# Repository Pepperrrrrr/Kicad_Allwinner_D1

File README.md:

# Kicad_Allwinner_D1

kicad测试全志D1高速PCB测试
kicad版本为kicad 6.0
未进行板上其他硬件测试，DDR满速测试完成

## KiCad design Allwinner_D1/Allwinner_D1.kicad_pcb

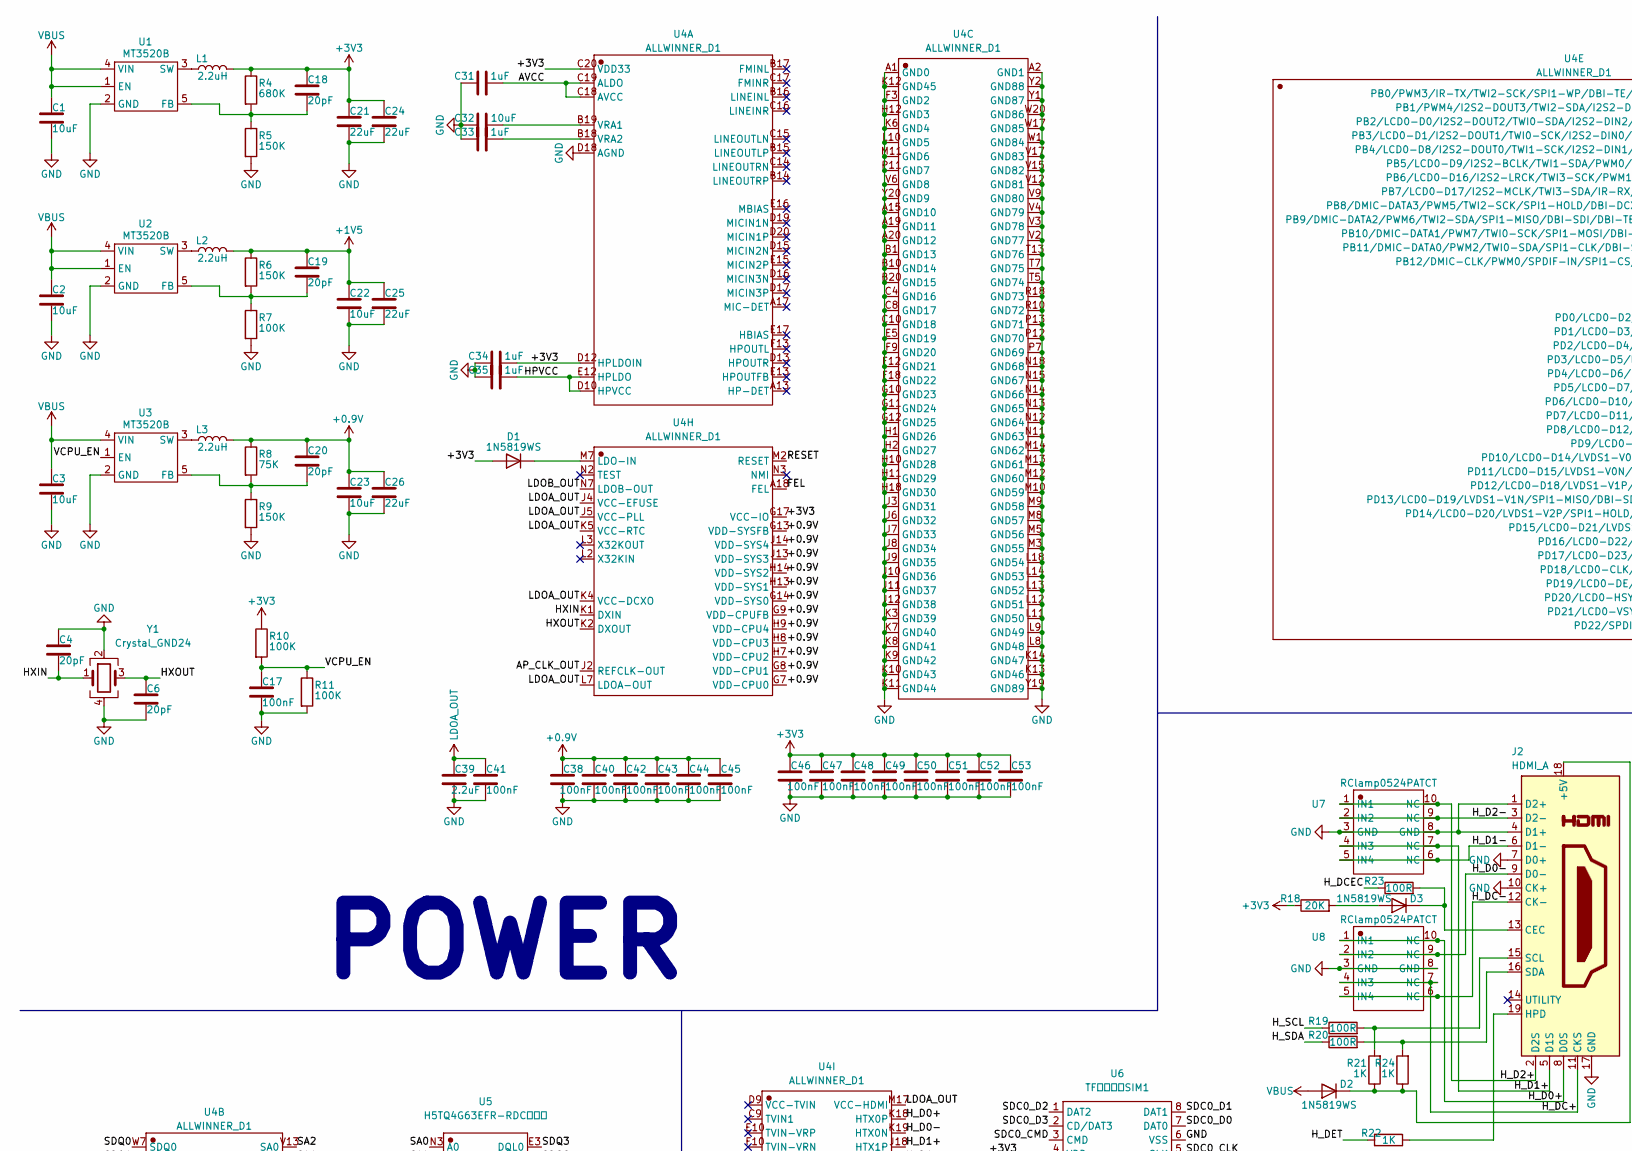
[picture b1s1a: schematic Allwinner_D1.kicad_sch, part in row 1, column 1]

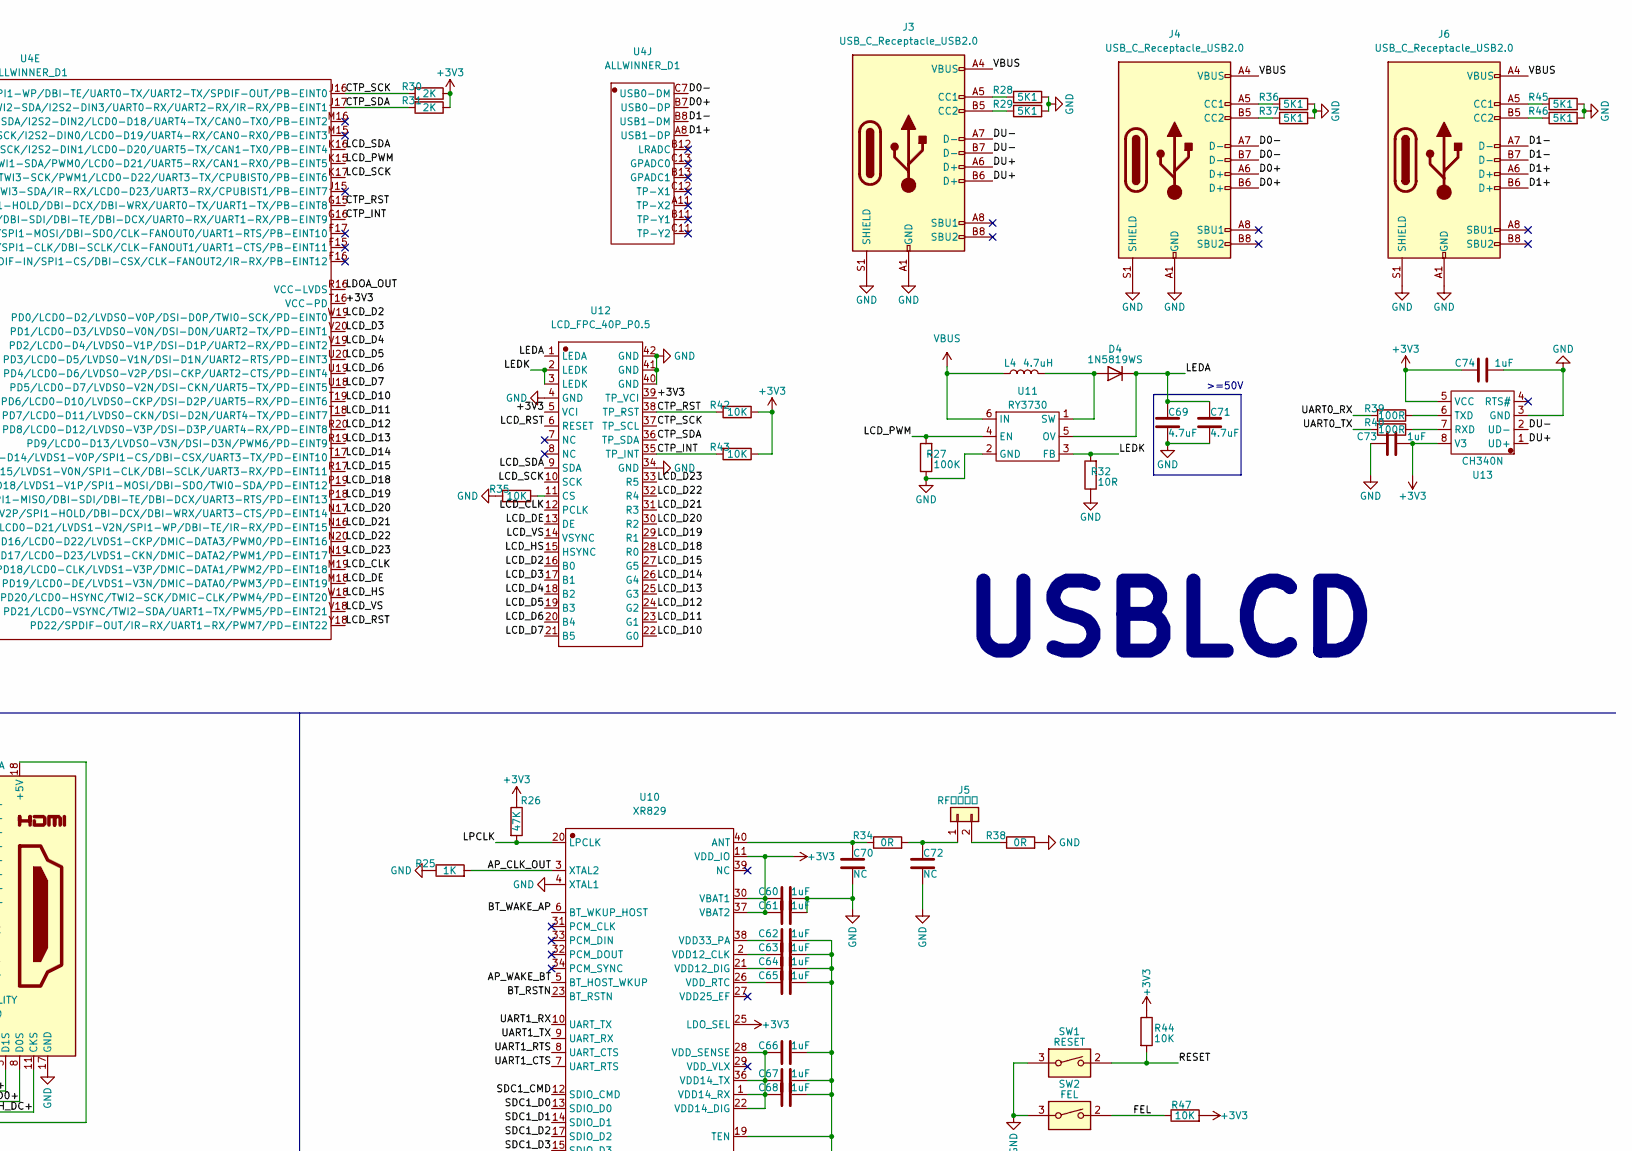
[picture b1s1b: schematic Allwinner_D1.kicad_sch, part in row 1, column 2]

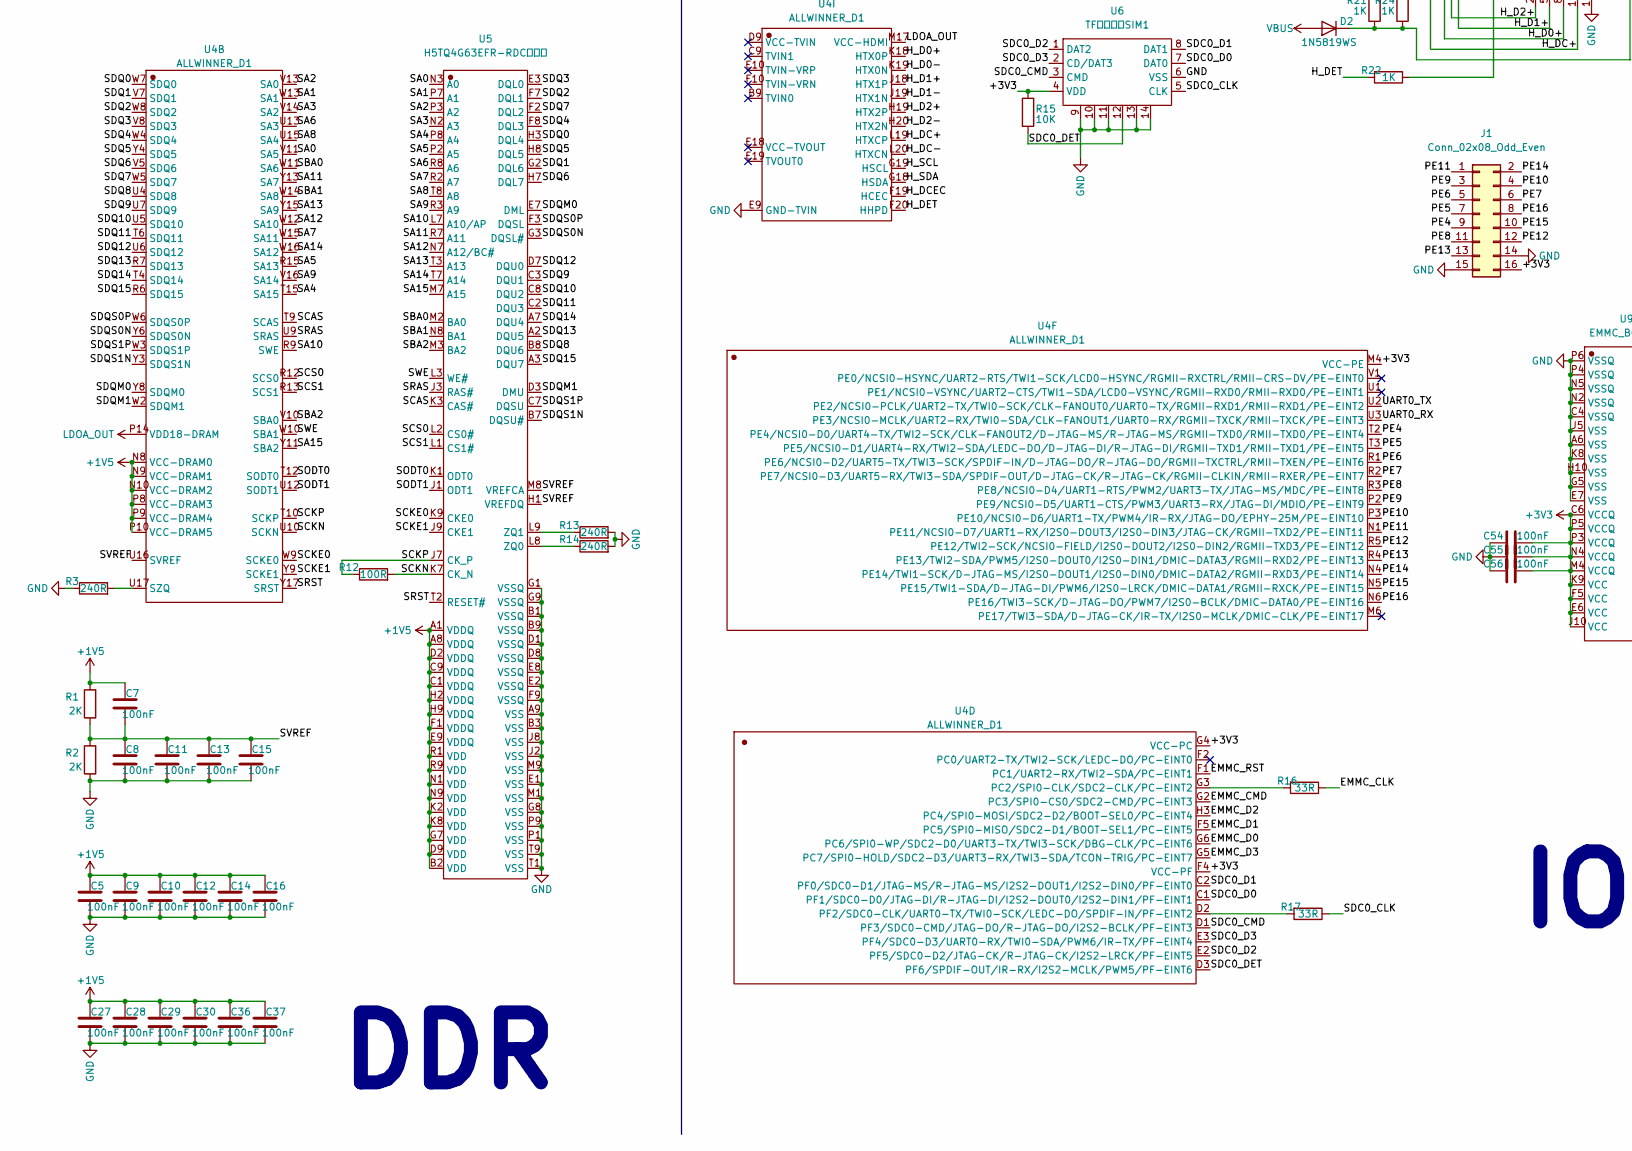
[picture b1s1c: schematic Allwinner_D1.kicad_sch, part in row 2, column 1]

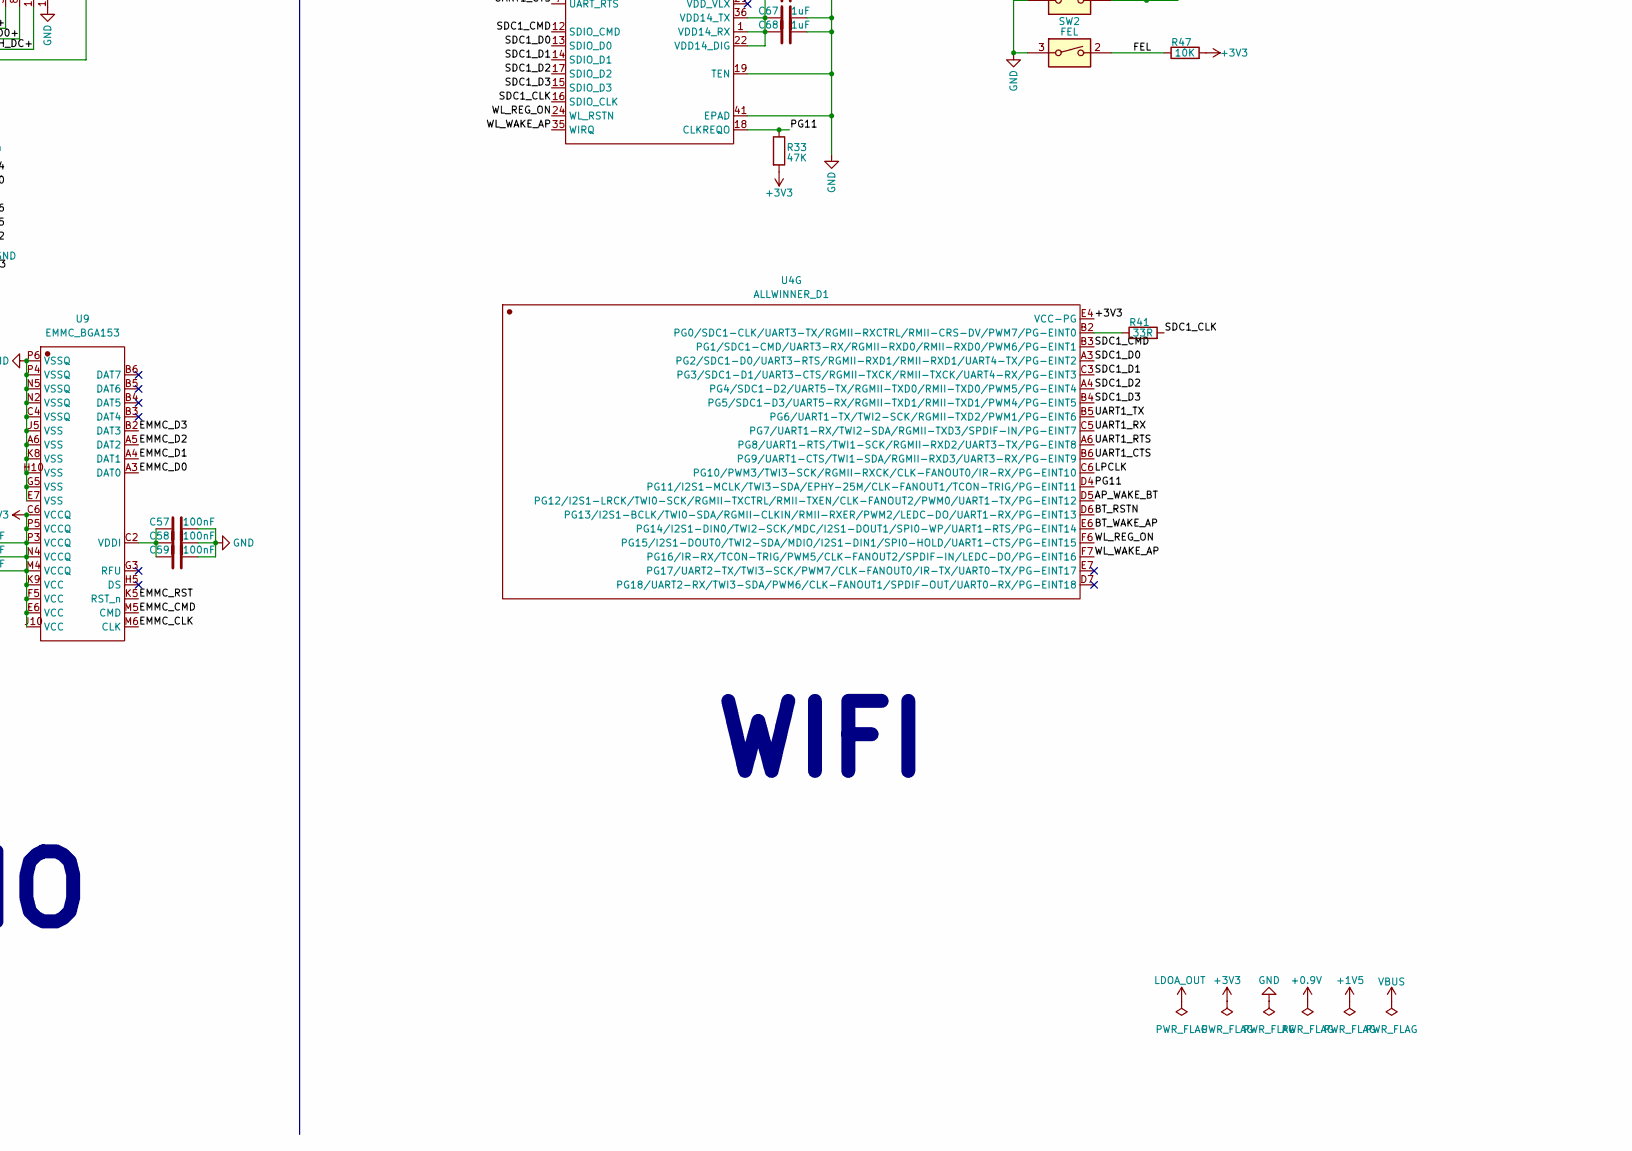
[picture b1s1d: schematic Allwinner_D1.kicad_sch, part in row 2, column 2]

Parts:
C1, C2, C3, C22, C23: 10uF; 0603_C
C4, C6, C18, C19, C20: 20pF; C0402
C5, C7, C8, C9, C10, C11, C12, C13, C14, C15, C16, C17, C27, C28, C29, C30, C36, C37, C38, C40, C41, C42, C43, C44, C45, C46, C47, C48, C49, C50, C51, C52, C53, C54, C55, C56, C57, C58, C59: 100nF; C0402
C21, C24, C25, C26: 22uF; 0603_C
C31, C33, C34, C35, C60, C61, C62, C63, C64, C65, C66, C67, C68, C73, C74: 1uF; C0402
C32: 10uF; C0402
C39: 2.2uF; C0402
C69, C71: 4.7uF; 0603_C
C70, C72: NC; C0402
D1, D2, D3, D4: 1N5819WS; SOD-323_L1.8-W1.3-LS2.5-RD
J1: Conn_02x08_Odd_Even; FPC-SMD_P0.50-16P_F0500WV-S
J2: HDMI_A; HDMI-SMD_HD219F-3D05200
J3, J4, J6: USB_C_Receptacle_USB2.0; USB_C_Receptacle_HRO_TYPE-C-31-M-12
J5: RF陶瓷天线; FILTER-SMD_1206-2P-L3.2-W1.6-L
L1, L2, L3: 2.2uH; IND-SMD_L2.0-W1.6
L4: 4.7uH; IND-SMD_L2.0-W1.6
R1, R2, R30, R31: 2K; R0402
R3, R13, R14: 240R; R0402
R4: 680K; R0402
R5, R6, R9: 150K; R0402
R7, R10, R11, R27: 100K; R0402
R8: 75K; R0402
R12, R19, R20, R23, R39, R40: 100R; R0402
R15, R35, R42, R43, R44, R47: 10K; R0402
R16, R17, R41: 33R; R0402
R18: 20K; R0402
R21, R22, R24, R25: 1K; R0402
R26, R33: 47K; R0402
R28, R29, R36, R37, R45, R46: 5K1; R0402
R32: 10R; R0402
R34, R38: 0R; R0402
SW1: RESET; KEY-SMD_4P-L4.2-W3.2-P2.20-LS4.6
SW2: FEL; KEY-SMD_4P-L4.2-W3.2-P2.20-LS4.6
U1, U2, U3: MT3520B; SOT-23-5_L3.0-W1.7-P0.95-LS2.8-BR
U4: ALLWINNER_D1; 全志D1
U5: H5TQ4G63EFR-RDC海力士; TFBGA-96_L13.0-W7.5-R16-C6-P0.80-TL
U6: TF贴片卡座SIM1; SIM-SMD_8P-1040310811
U7, U8: RClamp0524PATCT; SLP2510P8_L2.5-W1.0-P0.50-BL
U9: EMMC_BGA153; FBGA-153_L13.0-W11.5-P0.50_KLMAG1JETD-B041
U10: XR829; QFN-40_L5.0-W5.0-P0.40-BL-EP3.4
U11: RY3730; SOT-23-6_L2.9-W1.6-P0.95-LS2.8-BL
U12: LCD_FPC_40P_P0.5; FPC-SMD_40P-P0.50_FPC-05F-40PH20
U13: CH340N; SOP-8_L5.0-W4.0-P1.27-LS6.0-BL
Y1: Crystal_GND24; Crystal_SMD_2016-4Pin_2.0x1.6mm

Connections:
+0.9V: C20.1, C23.1, C26.1, C38.1, C40.1, C42.1, C43.1, C44.1, C45.1, L3.2, R8.1, U4.G7 (VDD-CPU0), U4.G8 (VDD-CPU1), U4.G9 (VDD-CPUFB), U4.G13 (VDD-SYSFB), U4.G14 (VDD-SYS0), U4.H7 (VDD-CPU2), U4.H8 (VDD-CPU3), U4.H9 (VDD-CPU4), U4.H13 (VDD-SYS1), U4.H14 (VDD-SYS2), U4.J13 (VDD-SYS3), U4.J14 (VDD-SYS4)
+1V5: C5.1, C7.1, C9.1, C10.1, C12.1, C14.1, C16.1, C19.1, C22.1, C25.1, C27.1, C28.1, C29.1, C30.1, C36.1, C37.1, L2.2, R1.2, R6.1, U4.N8 (VCC-DRAM0), U4.N9 (VCC-DRAM1), U4.N10 (VCC-DRAM2), U4.P8 (VCC-DRAM3), U4.P9 (VCC-DRAM4), U4.P10 (VCC-DRAM5), U5.A1 (VDDQ), U5.A8 (VDDQ), U5.B2 (VDD), U5.C1 (VDDQ), U5.C9 (VDDQ), U5.D2 (VDDQ), U5.D9 (VDD), U5.E9 (VDDQ), U5.F1 (VDDQ), U5.G7 (VDD), U5.H2 (VDDQ), U5.H9 (VDDQ), U5.K2 (VDD), U5.K8 (VDD), U5.N1 (VDD), U5.N9 (VDD), U5.R1 (VDD), U5.R9 (VDD)
+3V3: C18.1, C21.1, C24.1, C34.2, C46.1, C47.1, C48.1, C49.1, C50.1, C51.1, C52.1, C53.1, C54.2, C55.2, C56.2, C60.1, C61.1, C73.2, C74.1, D1.2 (A), J1.16, L1.2, R4.1, R10.1, R15.1, R18.1, R26.1, R30.1, R31.1, R33.2, R42.1, R43.1, R44.1, R47.2, U4.C20 (VDD33), U4.D12 (HPLDOIN), U4.E4 (VCC-PG), U4.F4 (VCC-PF), U4.G4 (VCC-PC), U4.G17 (VCC-IO), U4.M4 (VCC-PE), U4.T16 (VCC-PD), U6.4 (VDD), U9.C6 (VCCQ), U9.E6 (VCC), U9.F5 (VCC), U9.J10 (VCC), U9.K9 (VCC), U9.M4 (VCCQ), U9.N4 (VCCQ), U9.P3 (VCCQ), U9.P5 (VCCQ), U10.11 (VDD_IO), U10.25 (LDO_SEL), U10.30 (VBAT1), U10.37 (VBAT2), U12.5 (VCI), U12.39 (TP_VCI), U13.5 (VCC), U13.8 (V3)
/AP_CLK_OUT: R25.2, U4.J2 (REFCLK-OUT), U10.3 (XTAL2)
/AP_WAKE_BT: U4.D5 (PG12/I2S1-LRCK/TWI0-SCK/RGMII-TXCTRL/RM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), U10.5 (BT_HOST_WKUP)
/AVCC: C31.2, U4.C18 (AVCC), U4.C19 (ALDO)
/BT_RSTN: U4.D6 (PG13/I2S1-BCLK/TWI0-SDA/RGMII-CLKIN/RMI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), U10.23 (BT_RSTN)
/BT_WAKE_AP: U4.E6 (PG14/I2S1-DIN0/TWI2-SCK/MDC/I2S1-DOUT1/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), U10.6 (BT_WKUP_HOST)
/CTP_INT: R43.2, U4.G16 (PB9/DMIC-DATA2/PWM6/TWI2-SDA/SPI1-MISO/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), U12.35 (TP_INT)
/CTP_RST: R42.2, U4.G15 (PB8/DMIC-DATA3/PWM5/TWI2-SCK/SPI1-HOLD/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), U12.38 (TP_RST)
/CTP_SCK: R30.2, U4.J16 (PB0/PWM3/IR-TX/TWI2-SCK/SPI1-WP/DBI-TE/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), U12.37 (TP_SCL)
/CTP_SDA: R31.2, U4.J17 (PB1/PWM4/I2S2-DOUT3/TWI2-SDA/I2S2-DIN3/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), U12.36 (TP_SDA)
/D0+: J4.A6 (D+), J4.B6 (D+), U4.B7 (USB0-DP)
/D0-: J4.A7 (D-), J4.B7 (D-), U4.C7 (USB0-DM)
/D1+: J6.A6 (D+), J6.B6 (D+), U4.A8 (USB1-DP)
/D1-: J6.A7 (D-), J6.B7 (D-), U4.B8 (USB1-DM)
/DU+: J3.A6 (D+), J3.B6 (D+), U13.1 (UD+)
/DU-: J3.A7 (D-), J3.B7 (D-), U13.2 (UD-)
/EMMC_CLK: R16.1, U9.M6 (CLK)
/EMMC_CMD: U4.G2 (PC3/SPI0-CS0/SDC2-CMD/PC-EINT3), U9.M5 (CMD)
/EMMC_D0: U4.G6 (PC6/SPI0-WP/SDC2-D0/UART3-TX/TWI3-SCK/D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), U9.A3 (DAT0)
/EMMC_D1: U4.F5 (PC5/SPI0-MISO/SDC2-D1/BOOT-SEL1/PC-EINT5), U9.A4 (DAT1)
/EMMC_D2: U4.H3 (PC4/SPI0-MOSI/SDC2-D2/BOOT-SEL0/PC-EINT4), U9.A5 (DAT2)
/EMMC_D3: U4.G5 (PC7/SPI0-HOLD/SDC2-D3/UART3-RX/TWI3-SDA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), U9.B2 (DAT3)
/EMMC_RST: U4.F1 (PC1/UART2-RX/TWI2-SDA/PC-EINT1), U9.K5 (RST_n)
/FEL: R47.1, SW2.2, U4.A18 (FEL)
/HPVCC: C35.2, U4.D10 (HPVCC), U4.E12 (HPLDO)
/HXIN: C4.2, U4.K1 (DXIN), Y1.1
/HXOUT: C6.1, U4.K2 (DXOUT), Y1.3
/H_D0+: J2.8 (D0S), U4.K18 (HTX0P), U8.1 (IN1), U8.10 (NC)
/H_D0-: J2.9 (D0-), U4.K19 (HTX0N), U8.2 (IN2), U8.9 (NC)
/H_D1+: J2.5 (D1S), U4.J18 (HTX1P), U7.4 (IN3), U7.7 (NC)
/H_D1-: J2.6 (D1-), U4.J19 (HTX1N), U7.5 (IN4), U7.6 (NC)
/H_D2+: J2.2 (D2S), U4.H19 (HTX2P), U7.1 (IN1), U7.10 (NC)
/H_D2-: J2.3 (D2-), U4.H20 (HTX2N), U7.2 (IN2), U7.9 (NC)
/H_DC+: J2.11 (CKS), U4.L19 (HTXCP), U8.4 (IN3), U8.7 (NC)
/H_DC-: J2.12 (CK-), U4.L20 (HTXCN), U8.5 (IN4), U8.6 (NC)
/H_DCEC: R23.1, U4.F19 (HCEC)
/H_DET: R22.2, U4.F20 (HHPD)
/H_SCL: R19.1, U4.G19 (HSCL)
/H_SDA: R20.1, U4.G18 (HSDA)
/LCD_CLK: U4.M19 (PD18/LCD0-CLK/LVDS1-V3P/DMIC-DATA1/PWM2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), U12.12 (PCLK)
/LCD_D2: U4.W19 (PD0/LCD0-D2/LVDS0-V0P/DSI-D0P/TWI0-SCK/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), U12.16 (B0)
/LCD_D3: U4.V20 (PD1/LCD0-D3/LVDS0-V0N/DSI-D0N/UART2-TX/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), U12.17 (B1)
/LCD_D4: U4.V19 (PD2/LCD0-D4/LVDS0-V1P/DSI-D1P/UART2-RX/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), U12.18 (B2)
/LCD_D5: U4.U20 (PD3/LCD0-D5/LVDS0-V1N/DSI-D1N/UART2-RTS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), U12.19 (B3)
/LCD_D6: U4.U19 (PD4/LCD0-D6/LVDS0-V2P/DSI-CKP/UART2-CTS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), U12.20 (B4)
/LCD_D7: U4.U18 (PD5/LCD0-D7/LVDS0-V2N/DSI-CKN/UART5-TX/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), U12.21 (B5)
/LCD_D10: U4.T19 (PD6/LCD0-D10/LVDS0-CKP/DSI-D2P/UART5-RX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), U12.22 (G0)
/LCD_D11: U4.T18 (PD7/LCD0-D11/LVDS0-CKN/DSI-D2N/UART4-TX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), U12.23 (G1)
/LCD_D12: U4.R20 (PD8/LCD0-D12/LVDS0-V3P/DSI-D3P/UART4-RX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), U12.24 (G2)
/LCD_D13: U4.R19 (PD9/LCD0-D13/LVDS0-V3N/DSI-D3N/PWM6/PD-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), U12.25 (G3)
/LCD_D14: U4.T17 (PD10/LCD0-D14/LVDS1-V0P/SPI1-CS/DBI-CSX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), U12.26 (G4)
/LCD_D15: U4.R17 (PD11/LCD0-D15/LVDS1-V0N/SPI1-CLK/DBI-SC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), U12.27 (G5)
/LCD_D18: U4.P19 (PD12/LCD0-D18/LVDS1-V1P/SPI1-MOSI/DBI-S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), U12.28 (R0)
/LCD_D19: U4.P18 (PD13/LCD0-D19/LVDS1-V1N/SPI1-MISO/DBI-S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), U12.29 (R1)
/LCD_D20: U4.N17 (PD14/LCD0-D20/LVDS1-V2P/SPI1-HOLD/DBI-D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), U12.30 (R2)
/LCD_D21: U4.N16 (PD15/LCD0-D21/LVDS1-V2N/SPI1-WP/DBI-TE/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), U12.31 (R3)
/LCD_D22: U4.N20 (PD16/LCD0-D22/LVDS1-CKP/DMIC-DATA3/PWM0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), U12.32 (R4)
/LCD_D23: U4.N19 (PD17/LCD0-D23/LVDS1-CKN/DMIC-DATA2/PWM1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), U12.33 (R5)
/LCD_DE: U4.M18 (PD19/LCD0-DE/LVDS1-V3N/DMIC-DATA0/PWM3/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), U12.13 (DE)
/LCD_HS: U4.W18 (PD20/LCD0-HSYNC/TWI2-SCK/DMIC-CLK/PWM4/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), U12.15 (HSYNC)
/LCD_PWM: R27.2, U4.K15 (PB5/LCD0-D9/I2S2-BCLK/TWI1-SDA/PWM0/LCD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), U11.4 (EN)
/LCD_RST: U4.Y18 (PD22/SPDIF-OUT/IR-RX/UART1-RX/PWM7/PD-E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), U12.6 (RESET)
/LCD_SCK: U4.K17 (PB6/LCD0-D16/I2S2-LRCK/TWI3-SCK/PWM1/LC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), U12.10 (SCK)
/LCD_SDA: U4.K16 (PB4/LCD0-D8/I2S2-DOUT0/TWI1-SCK/I2S2-DI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), U12.9 (SDA)
/LCD_VS: U4.V18 (PD21/LCD0-VSYNC/TWI2-SDA/UART1-TX/PWM5/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), U12.14 (VSYNC)
/LDOB_OUT: U4.N7 (LDOB-OUT)
/LEDA: C69.1, C71.1, D4.1 (K), U11.5 (OV), U12.1 (LEDA)
/LEDK: R32.2, U11.3 (FB), U12.2 (LEDK), U12.3 (LEDK)
/LPCLK: R26.2, U4.C6 (PG10/PWM3/TWI3-SCK/RGMII-RXCK/CLK-FANOU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), U10.20 (LPCLK)
/PE4: J1.9, U4.T2 (PE4/NCSI0-D0/UART4-TX/TWI2-SCK/CLK-FANO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)
/PE5: J1.7, U4.T3 (PE5/NCSI0-D1/UART4-RX/TWI2-SDA/LEDC-DO/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)
/PE6: J1.5, U4.R1 (PE6/NCSI0-D2/UART5-TX/TWI3-SCK/SPDIF-IN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)
/PE7: J1.6, U4.R2 (PE7/NCSI0-D3/UART5-RX/TWI3-SDA/SPDIF-OU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)
/PE8: J1.11, U4.R3 (PE8/NCSI0-D4/UART1-RTS/PWM2/UART3-TX/JT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)
/PE9: J1.3, U4.P2 (PE9/NCSI0-D5/UART1-CTS/PWM3/UART3-RX/JT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)
/PE10: J1.4, U4.P3 (PE10/NCSI0-D6/UART1-TX/PWM4/IR-RX/JTAG-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)
/PE11: J1.1, U4.N1 (PE11/NCSI0-D7/UART1-RX/I2S0-DOUT3/I2S0-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)
/PE12: J1.12, U4.R5 (PE12/TWI2-SCK/NCSI0-FIELD/I2S0-DOUT2/I2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)
/PE13: J1.13, U4.R4 (PE13/TWI2-SDA/PWM5/I2S0-DOUT0/I2S0-DIN1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)
/PE14: J1.2, U4.N4 (PE14/TWI1-SCK/D-JTAG-MS/I2S0-DOUT1/I2S0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)
/PE15: J1.10, U4.N5 (PE15/TWI1-SDA/D-JTAG-DI/PWM6/I2S0-LRCK/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)
/PE16: J1.8, U4.N6 (PE16/TWI3-SCK/D-JTAG-DO/PWM7/I2S0-BCLK/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)
/PG11: R33.1, U4.D4 (PG11/I2S1-MCLK/TWI3-SDA/EPHY-25M/CLK-FA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), U10.18 (CLKREQO)
/RESET: R44.2, SW1.2, U4.M2 (RESET)
/SA0: U4.V11 (SA5), U5.N3 (A0)
/SA1: U4.W13 (SA1), U5.P7 (A1)
/SA2: U4.V13 (SA0), U5.P3 (A2)
/SA3: U4.V14 (SA2), U5.N2 (A3)
/SA4: U4.T15 (SA15), U5.P8 (A4)
/SA5: U4.R15 (SA13), U5.P2 (A5)
/SA6: U4.U13 (SA3), U5.R8 (A6)
/SA7: U4.W15 (SA11), U5.R2 (A7)
/SA8: U4.U15 (SA4), U5.T8 (A8)
/SA9: U4.V16 (SA14), U5.R3 (A9)
/SA10: U4.R9 (SWE), U5.L7 (A10/AP)
/SA11: U4.Y13 (SA7), U5.R7 (A11)
/SA12: U4.W12 (SA10), U5.N7 (A12/BC#)
/SA13: U4.Y15 (SA9), U5.T3 (A13)
/SA14: U4.W16 (SA12), U5.T7 (A14)
/SA15: U4.Y11 (SBA2), U5.M7 (A15)
/SBA0: U4.W11 (SA6), U5.M2 (BA0)
/SBA1: U4.W14 (SA8), U5.N8 (BA1)
/SBA2: U4.V10 (SBA0), U5.M3 (BA2)
/SCAS: U4.T9 (SCAS), U5.K3 (CAS#)
/SCKE0: U4.W9 (SCKE0), U5.K9 (CKE0)
/SCKE1: U4.Y9 (SCKE1), U5.J9 (CKE1)
/SCKN: R12.2, U4.U10 (SCKN), U5.K7 (CK_N)
/SCKP: R12.1, U4.T10 (SCKP), U5.J7 (CK_P)
/SCS0: U4.R12 (SCS0), U5.L2 (CS0#)
/SCS1: U4.R13 (SCS1), U5.L1 (CS1#)
/SDC0_CLK: R17.1, U6.5 (CLK)
/SDC0_CMD: U4.D1 (PF3/SDC0-CMD/JTAG-DO/R-JTAG-DO/I2S2-BCL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), U6.3 (CMD)
/SDC0_D0: U4.C1 (PF1/SDC0-D0/JTAG-DI/R-JTAG-DI/I2S2-DOUT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), U6.7 (DAT0)
/SDC0_D1: U4.C2 (PF0/SDC0-D1/JTAG-MS/R-JTAG-MS/I2S2-DOUT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), U6.8 (DAT1)
/SDC0_D2: U4.E2 (PF5/SDC0-D2/JTAG-CK/R-JTAG-CK/I2S2-LRCK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), U6.1 (DAT2)
/SDC0_D3: U4.E3 (PF4/SDC0-D3/UART0-RX/TWI0-SDA/PWM6/IR-T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), U6.2 (CD/DAT3)
/SDC0_DET: R15.2, U4.D3 (PF6/SPDIF-OUT/IR-RX/I2S2-MCLK/PWM5/PF-E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), U6.12
/SDC1_CLK: R41.2, U10.16 (SDIO_CLK)
/SDC1_CMD: U4.B3 (PG1/SDC1-CMD/UART3-RX/RGMII-RXD0/RMII-R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), U10.12 (SDIO_CMD)
/SDC1_D0: U4.A3 (PG2/SDC1-D0/UART3-RTS/RGMII-RXD1/RMII-R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), U10.13 (SDIO_D0)
/SDC1_D1: U4.C3 (PG3/SDC1-D1/UART3-CTS/RGMII-TXCK/RMII-T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), U10.14 (SDIO_D1)
/SDC1_D2: U4.A4 (PG4/SDC1-D2/UART5-TX/RGMII-TXD0/RMII-TX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), U10.17 (SDIO_D2)
/SDC1_D3: U4.B4 (PG5/SDC1-D3/UART5-RX/RGMII-TXD1/RMII-TX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), U10.15 (SDIO_D3)
/SDQ0: U4.W7 (SDQ0), U5.H3 (DQL4)
/SDQ1: U4.V7 (SDQ1), U5.G2 (DQL6)
/SDQ2: U4.W8 (SDQ2), U5.F7 (DQL1)
/SDQ3: U4.V8 (SDQ3), U5.E3 (DQL0)
/SDQ4: U4.W4 (SDQ4), U5.F8 (DQL3)
/SDQ5: U4.Y4 (SDQ5), U5.H8 (DQL5)
/SDQ6: U4.V5 (SDQ6), U5.H7 (DQL7)
/SDQ7: U4.W5 (SDQ7), U5.F2 (DQL2)
/SDQ8: U4.U4 (SDQ8), U5.B8 (DQU6)
/SDQ9: U4.U7 (SDQ9), U5.C3 (DQU1)
/SDQ10: U4.U5 (SDQ10), U5.C8 (DQU2)
/SDQ11: U4.T6 (SDQ11), U5.C2 (DQU3)
/SDQ12: U4.U6 (SDQ12), U5.D7 (DQU0)
/SDQ13: U4.R7 (SDQ13), U5.A2 (DQU5)
/SDQ14: U4.T4 (SDQ14), U5.A7 (DQU4)
/SDQ15: U4.R6 (SDQ15), U5.A3 (DQU7)
/SDQM0: U4.Y8 (SDQM0), U5.E7 (DML)
/SDQM1: U4.W2 (SDQM1), U5.D3 (DMU)
/SDQS0N: U4.Y6 (SDQS0N), U5.G3 (DQSL#)
/SDQS0P: U4.W6 (SDQS0P), U5.F3 (DQSL)
/SDQS1N: U4.Y3 (SDQS1N), U5.B7 (DQSU#)
/SDQS1P: U4.W3 (SDQS1P), U5.C7 (DQSU)
/SODT0: U4.T12 (SODT0), U5.K1 (ODT0)
/SODT1: U4.U12 (SODT1), U5.J1 (ODT1)
/SRAS: U4.U9 (SRAS), U5.J3 (RAS#)
/SRST: U4.Y17 (SRST), U5.T2 (RESET#)
/SWE: U4.W10 (SBA1), U5.L3 (WE#)
/UART0_RX: R39.2, U4.U3 (PE3/NCSI0-MCLK/UART2-RX/TWI0-SDA/CLK-FA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)
/UART0_TX: R40.2, U4.U2 (PE2/NCSI0-PCLK/UART2-TX/TWI0-SCK/CLK-FA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)
/UART1_CTS: U4.B6 (PG9/UART1-CTS/TWI1-SDA/RGMII-RXD3/UART3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), U10.7 (UART_RTS)
/UART1_RTS: U4.A6 (PG8/UART1-RTS/TWI1-SCK/RGMII-RXD2/UART3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), U10.8 (UART_CTS)
/UART1_RX: U4.C5 (PG7/UART1-RX/TWI2-SDA/RGMII-TXD3/SPDIF-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), U10.10 (UART_TX)
/UART1_TX: U4.B5 (PG6/UART1-TX/TWI2-SCK/RGMII-TXD2/PWM1/P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), U10.9 (UART_RX)
/VCPU_EN: C17.1, R10.2, R11.1, U3.1 (EN)
/WL_REG_ON: U4.F6 (PG15/I2S1-DOUT0/TWI2-SDA/MDIO/I2S1-DIN1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), U10.24 (WL_RSTN)
/WL_WAKE_AP: U4.F7 (PG16/IR-RX/TCON-TRIG/PWM5/CLK-FANOUT2/S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), U10.35 (WIRQ)
GND: C1.2, C2.2, C3.2, C4.1, C5.2, C6.2, C8.2, C9.2, C10.2, C11.2, C12.2, C13.2, C14.2, C15.2, C16.2, C17.2, C21.2, C22.2, C23.2, C24.2, C25.2, C26.2, C27.2, C28.2, C29.2, C30.2, C31.1, C32.1, C33.1, C34.1, C35.1, C36.2, C37.2, C38.2, C39.2, C40.2, C41.2, C42.2, C43.2, C44.2, C45.2, C46.2, C47.2, C48.2, C49.2, C50.2, C51.2, C52.2, C53.2, C54.1, C55.1, C56.1, C57.2, C58.2, C59.2, C60.2, C61.2, C62.2, C63.2, C64.2, C65.2, C66.2, C67.2, C68.2, C69.2, C70.2, C71.2, C72.2, C73.1, C74.2, J1.14, J1.15, J2.1 (D2+), J2.4 (D1+), J2.7 (D0+), J2.10 (CK+), J2.17 (GND), J2.20, J2.21, J2.22, J2.23, J3.A1 (GND), J3.A12 (GND), J3.B1 (GND), J3.B12 (GND), J3.S1 (SHIELD), J4.A1 (GND), J4.A12 (GND), J4.B1 (GND), J4.B12 (GND), J4.S1 (SHIELD), J6.A1 (GND), J6.A12 (GND), J6.B1 (GND), J6.B12 (GND), J6.S1 (SHIELD), R2.1, R3.1, R5.2, R7.2, R9.2, R11.2, R13.2, R14.2, R25.1, R27.1, R28.2, R29.2, R32.1, R35.2, R36.2, R37.2, R38.2, R45.2, R46.2, SW1.3, SW2.3, U1.2 (GND), U2.2 (GND), U3.2 (GND), U4.A1 (GND0), U4.A2 (GND1), U4.A15 (GND10), U4.A19 (GND11), U4.A20 (GND12), U4.B1 (GND13), U4.B10 (GND14), U4.B20 (GND15), U4.C4 (GND16), U4.C8 (GND17), U4.C10 (GND18), U4.D18 (AGND), U4.E5 (GND19), U4.E9 (GND-TVIN), U4.F3 (GND2), U4.F9 (GND20), U4.F12 (GND21), U4.F18 (GND22), U4.G10 (GND23), U4.G11 (GND24), U4.G12 (GND25), U4.H1 (GND26), U4.H2 (GND27), U4.H10 (GND28), U4.H11 (GND29), U4.H12 (GND3), U4.H18 (GND30), U4.J3 (GND31), U4.J6 (GND32), U4.J7 (GND33), U4.J8 (GND34), U4.J9 (GND35), U4.J10 (GND36), U4.J11 (GND37), U4.J12 (GND38), U4.K3 (GND39), U4.K6 (GND4), U4.K7 (GND40), U4.K8 (GND41), U4.K9 (GND42), U4.K10 (GND43), U4.K11 (GND44), U4.K12 (GND45), U4.K13 (GND46), U4.K14 (GND47), U4.L8 (GND48), U4.L9 (GND49), U4.L10 (GND5), U4.L11 (GND50), U4.L12 (GND51), U4.L13 (GND52), U4.L14 (GND53), U4.L18 (GND54), U4.M3 (GND55), U4.M5 (GND56), U4.M8 (GND57), U4.M9 (GND58), U4.M10 (GND59), U4.M11 (GND6), U4.M12 (GND60), U4.M13 (GND61), U4.M14 (GND62), U4.N11 (GND63), U4.N12 (GND64), U4.N13 (GND65), U4.N14 (GND66), U4.N15 (GND67), U4.N18 (GND68), U4.P7 (GND69), U4.P11 (GND7), U4.P12 (GND70), U4.P13 (GND71), U4.R10 (GND72), U4.R18 (GND73), U4.T5 (GND74), U4.T7 (GND75), U4.T13 (GND76), U4.V2 (GND77), U4.V3 (GND78), U4.V4 (GND79), U4.V6 (GND8), U4.V9 (GND80), U4.V12 (GND81), U4.V15 (GND82), U4.V17 (GND83), U4.W1 (GND84), U4.W17 (GND85), U4.W20 (GND86), U4.Y1 (GND87), U4.Y2 (GND88), U4.Y19 (GND89), U4.Y20 (GND9), U5.A9 (VSS), U5.B1 (VSSQ), U5.B3 (VSS), U5.B9 (VSSQ), U5.D1 (VSSQ), U5.D8 (VSSQ), U5.E1 (VSS), U5.E2 (VSSQ), U5.E8 (VSSQ), U5.F9 (VSSQ), U5.G1 (VSSQ), U5.G8 (VSS), U5.G9 (VSSQ), U5.J2 (VSS), U5.J8 (VSS), U5.M1 (VSS), U5.M9 (VSS), U5.P1 (VSS), U5.P9 (VSS), U5.T1 (VSS), U5.T9 (VSS), U6.6 (VSS), U6.9, U6.10, U6.11, U6.13, U6.14, U7.3 (GND), U7.8 (GND), U8.3 (GND), U8.8 (GND), U9.A6 (VSS), U9.C4 (VSSQ), U9.E7 (VSS), U9.G5 (VSS), U9.H10 (VSS), U9.J5 (VSS), U9.K8 (VSS), U9.N2 (VSSQ), U9.N5 (VSSQ), U9.P4 (VSSQ), U9.P6 (VSSQ), U10.4 (XTAL1), U10.19 (TEN), U10.41 (EPAD), U11.2 (GND), U12.4 (GND), U12.34 (GND), U12.40 (GND), U12.41 (GND), U12.42 (GND), U13.3 (GND), Y1.2, Y1.4
LDOA_OUT: C39.1, C41.1, U4.J4 (VCC-EFUSE), U4.J5 (VCC-PLL), U4.K4 (VCC-DCXO), U4.K5 (VCC-RTC), U4.L7 (LDOA-OUT), U4.M17 (VCC-HDMI), U4.P14 (VDD18-DRAM), U4.R16 (VCC-LVDS)
unnamed: C18.2, R4.2, R5.1, U1.5 (FB)
unnamed: C19.2, R6.2, R7.1, U2.5 (FB)
unnamed: C20.2, R8.2, R9.1, U3.5 (FB)
unnamed: C32.2, U4.B19 (VRA1)
unnamed: C33.2, U4.B18 (VRA2)
unnamed: C57.1, C58.1, C59.1, U9.C2 (VDDI)
unnamed: C62.1, U10.38 (VDD33_PA)
unnamed: C63.1, U10.2 (VDD12_CLK)
unnamed: C64.1, U10.21 (VDD12_DIG)
unnamed: C65.1, U10.26 (VDD_RTC)
unnamed: C66.1, C67.1, C68.1, U10.1 (VDD14_RX), U10.22 (VDD14_DIG), U10.28 (VDD_SENSE), U10.36 (VDD14_TX)
unnamed: C70.1, R34.1, U10.40 (ANT)
unnamed: C72.1, J5.1, R34.2
unnamed: D1.1 (K), U4.M7 (LDO-IN)
unnamed: D2.1 (K), J2.18 (+5V), R21.1, R24.1
unnamed: D3.1 (K), J2.13 (CEC), R23.2
unnamed: D3.2 (A), R18.2
unnamed: D4.2 (A), L4.2, U11.1 (SW)
unnamed: J2.15 (SCL), R19.2, R21.2
unnamed: J2.16 (SDA), R20.2, R24.2
unnamed: J2.19 (HPD), R22.1
unnamed: J3.A5 (CC1), R28.1
unnamed: J3.B5 (CC2), R29.1
unnamed: J4.A5 (CC1), R36.1
unnamed: J4.B5 (CC2), R37.1
unnamed: J5.2, R38.1
unnamed: J6.A5 (CC1), R45.1
unnamed: J6.B5 (CC2), R46.1
unnamed: L1.1, U1.3 (SW)
unnamed: L2.1, U2.3 (SW)
unnamed: L3.1, U3.3 (SW)
unnamed: R3.2, U4.U17 (SZQ)
unnamed: R13.1, U5.L9 (ZQ1)
unnamed: R14.1, U5.L8 (ZQ0)
unnamed: R16.2, U4.G3 (PC2/SPI0-CLK/SDC2-CLK/PC-EINT2)
unnamed: R17.2, U4.D2 (PF2/SDC0-CLK/UART0-TX/TWI0-SCK/LEDC-DO/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)
unnamed: R35.1, U12.11 (CS)
unnamed: R39.1, U13.6 (TXD)
unnamed: R40.1, U13.7 (RXD)
unnamed: R41.1, U4.B2 (PG0/SDC1-CLK/UART3-TX/RGMII-RXCTRL/RMII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)
VBUS: C1.1, C2.1, C3.1, D2.2 (A), J3.A4 (VBUS), J3.A9 (VBUS), J3.B4 (VBUS), J3.B9 (VBUS), J4.A4 (VBUS), J4.A9 (VBUS), J4.B4 (VBUS), J4.B9 (VBUS), J6.A4 (VBUS), J6.A9 (VBUS), J6.B4 (VBUS), J6.B9 (VBUS), L4.1, U1.1 (EN), U1.4 (VIN), U2.1 (EN), U2.4 (VIN), U3.4 (VIN), U11.6 (IN)

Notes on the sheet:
WIFI
DDR
POWER
USBLCD
>=50V

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
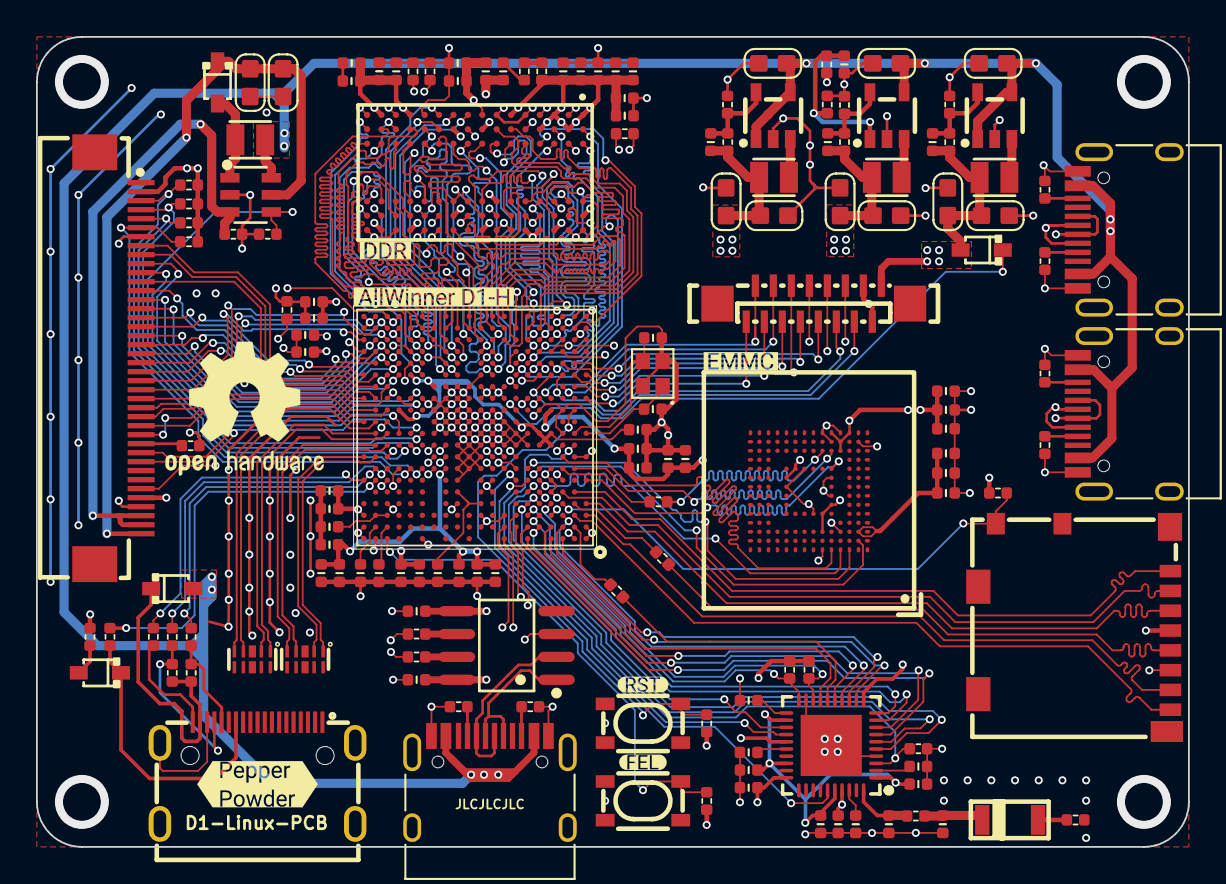
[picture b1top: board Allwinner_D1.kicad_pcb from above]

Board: 6 copper layers, 64.0 x 45.0 mm, 157 parts (0 on the bottom side), 205 nets.

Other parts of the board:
kibuzzard-633FF4E3: G***; kibuzzard-633FF4E3
kibuzzard-633FF4F1: G***; kibuzzard-633FF4F1
kibuzzard-633FF5C5: G***; kibuzzard-633FF5C5
kibuzzard-633FF5E4: G***; kibuzzard-633FF5E4
kibuzzard-633FF9FA: G***; kibuzzard-633FF9FA
kibuzzard-633FF59A: G***; kibuzzard-633FF59A

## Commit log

2025-05-31 download tool
    全志D1下载工具
2025-05-31 Kicad设计全志D1PCB
2025-05-31 DragonHD tool
